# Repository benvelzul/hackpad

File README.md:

# HACKPAD

This hackpad is a 4x4 that has a rotary encoder. 

ITs got 2 layers the first layer is like normal numpad while the second is for the mediaplayer and everything that needs shortcuts that a 65% keyborad doesnt have (my laptop doesnt have) 

My Schematic: 

My PCB: 

My case:

PCB and case: 

If u want to check my onshape here it is (sorry if its really messy): https://cad.onshape.com/documents/7955f6143054f35a25e47023/w/3cc283572c9fd03e1a13d1ab/e/2172772127661373bbc4b207 

## Firmware

I made the firmware with KMK firmware thingy. 

So i just coded it instead of using the QMK config.

## BOM
here is what u need to make my amazing hackpad
- 15x Cherry MX Switches
- 15x DSA Keycaps
- 16x 1N4148 DO-35 Diodes.
- 1x EC11 Rotary Encoder
- 1x XIAO RP2040
- 1x Case
-

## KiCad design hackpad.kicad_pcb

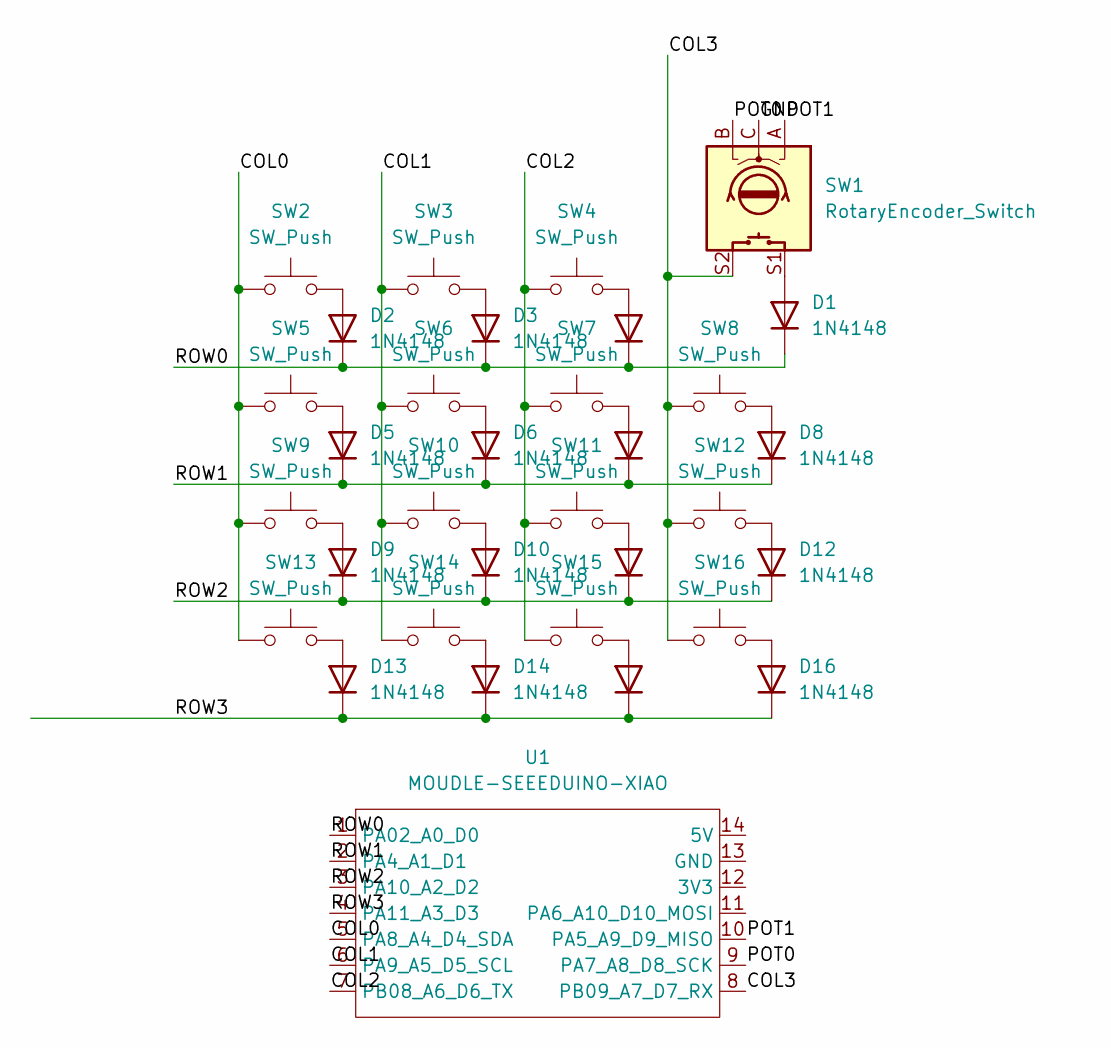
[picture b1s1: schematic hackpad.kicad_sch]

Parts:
D1, D2, D3, D4, D5, D6, D7, D8, D9, D10, D11, D12, D13, D14, D15, D16: 1N4148; D_DO-35_SOD27_P7.62mm_Horizontal
SW1: RotaryEncoder_Switch; RotaryEncoder_Alps_EC11E-Switch_Vertical_H20mm
SW2, SW3, SW4, SW5, SW6, SW7, SW8, SW9, SW10, SW11, SW12, SW13, SW14, SW15, SW16: SW_Push; SW_MX_1u
U1: MOUDLE-SEEEDUINO-XIAO; XIAO-Generic-Hybrid-14P-2.54-21X17.8MM

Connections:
/COL0: SW2.1, SW5.1, SW9.1, SW13.1, U1.5 (PA8_A4_D4_SDA)
/COL1: SW3.1, SW6.1, SW10.1, SW14.1, U1.6 (PA9_A5_D5_SCL)
/COL2: SW4.1, SW7.1, SW11.1, SW15.1, U1.7 (PB08_A6_D6_TX)
/COL3: SW1.S2, SW8.1, SW12.1, SW16.1, U1.8 (PB09_A7_D7_RX)
/GND: SW1.C
/POT0: SW1.B, U1.9 (PA7_A8_D8_SCK)
/POT1: SW1.A, U1.10 (PA5_A9_D9_MISO)
/ROW0: D1.1 (K), D2.1 (K), D3.1 (K), D4.1 (K), U1.1 (PA02_A0_D0)
/ROW1: D5.1 (K), D6.1 (K), D7.1 (K), D8.1 (K), U1.2 (PA4_A1_D1)
/ROW2: D9.1 (K), D10.1 (K), D11.1 (K), D12.1 (K), U1.3 (PA10_A2_D2)
/ROW3: D13.1 (K), D14.1 (K), D15.1 (K), D16.1 (K), U1.4 (PA11_A3_D3)
unnamed: D1.2 (A), SW1.S1
unnamed: D2.2 (A), SW2.2
unnamed: D3.2 (A), SW3.2
unnamed: D4.2 (A), SW4.2
unnamed: D5.2 (A), SW5.2
unnamed: D6.2 (A), SW6.2
unnamed: D7.2 (A), SW7.2
unnamed: D8.2 (A), SW8.2
unnamed: D9.2 (A), SW9.2
unnamed: D10.2 (A), SW10.2
unnamed: D11.2 (A), SW11.2
unnamed: D12.2 (A), SW12.2
unnamed: D13.2 (A), SW13.2
unnamed: D14.2 (A), SW14.2
unnamed: D15.2 (A), SW15.2
unnamed: D16.2 (A), SW16.2

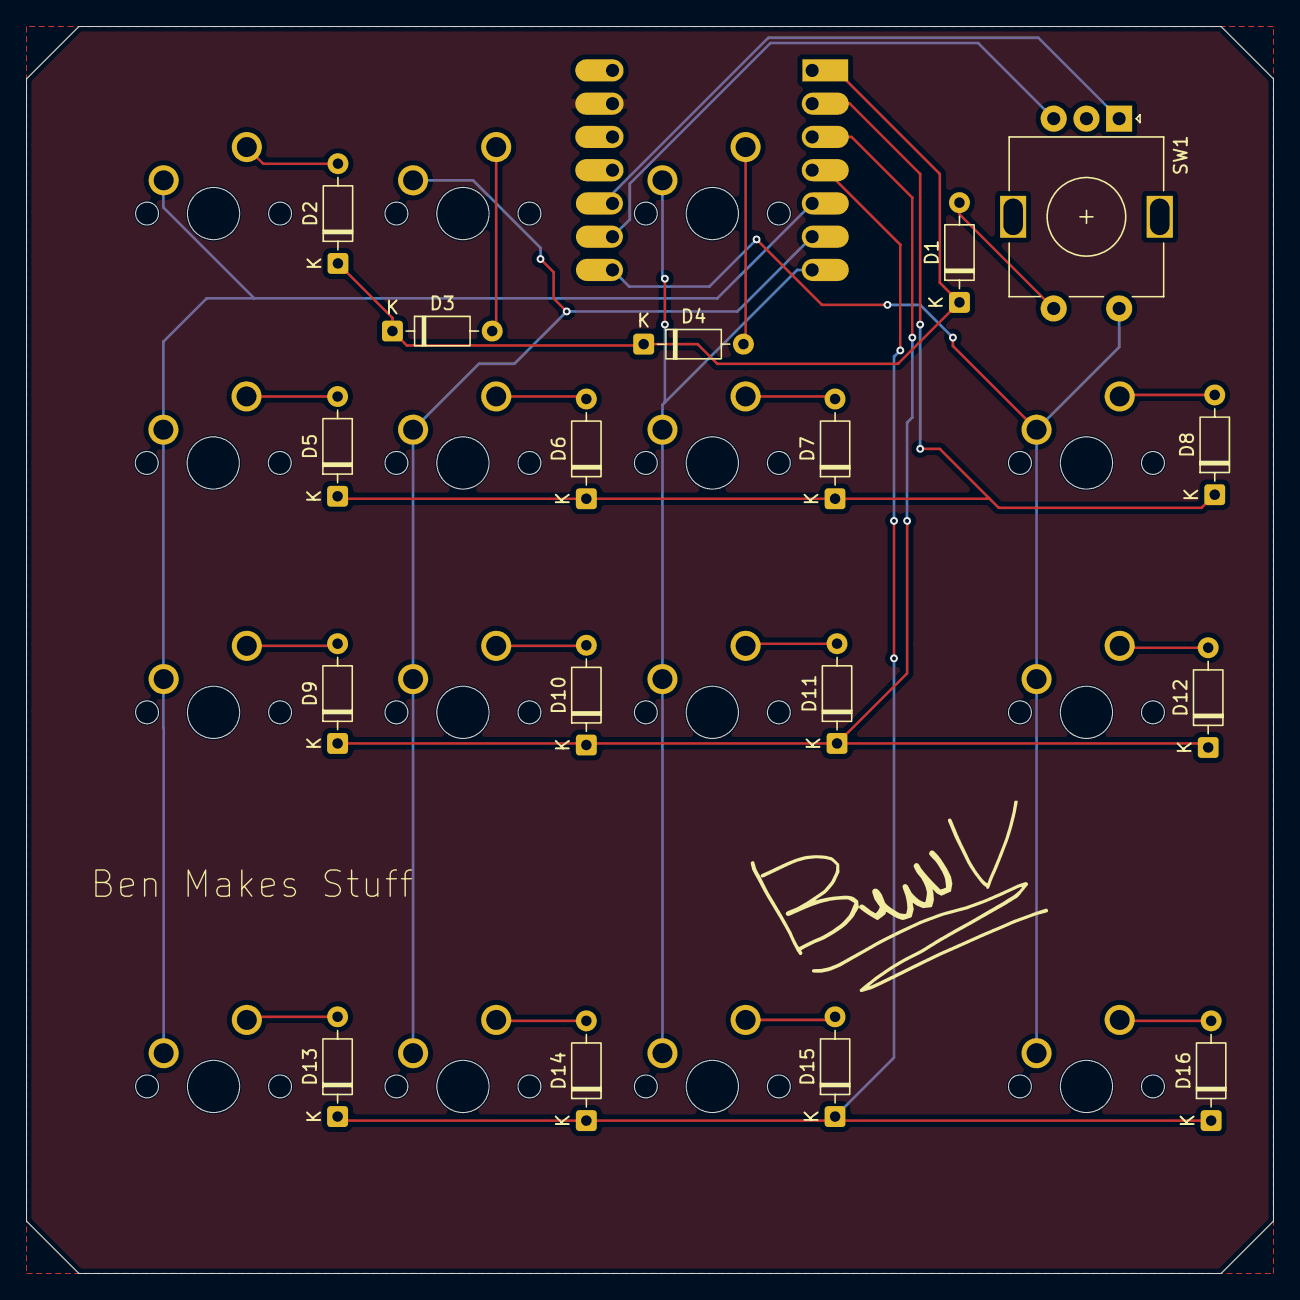
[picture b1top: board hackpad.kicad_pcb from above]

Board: 2 copper layers, 95.3 x 95.2 mm, 34 parts (1 on the bottom side), 26 nets.

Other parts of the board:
 : LOGO

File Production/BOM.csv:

"Reference","Qty","Value","DNP","Exclude from BOM","Exclude from Board","Footprint","Datasheet"
"D1,D2,D3,D4,D5,D6,D7,D8,D9,D10,D11,D12,D13,D14,D15,D16","16","1N4148","","","","Diode_THT:D_DO-35_SOD27_P7.62mm_Horizontal","https://assets.nexperia.com/documents/data-sheet/1N4148_1N4448.pdf"
"SW1","1","RotaryEncoder_Switch","","","","Rotary_Encoder:RotaryEncoder_Alps_EC11E-Switch_Vertical_H20mm",""
"SW2,SW3,SW4,SW5,SW6,SW7,SW8,SW9,SW10,SW11,SW12,SW13,SW14,SW15,SW16","15","SW_Push","","","","PCM_marbastlib-mx:SW_MX_1u",""
"U1","1","MOUDLE-SEEEDUINO-XIAO","","","","hackclub_lib:XIAO-Generic-Hybrid-14P-2.54-21X17.8MM",""
